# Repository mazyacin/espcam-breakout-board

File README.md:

# espcam-breakout-board
high-end ESP32-Cam breakout-board for IOT and monetering systems , so there has been a problem with the espcam and its the programming because it does not have a USB to UART converter so i am making a breakout board for it that solves that problem and adds more features like :tp5100 for charging ,MT3608 for 5v,3.3v,output, bme280 for IOT  also an IMU mpu6000 ,BMS( DW01A protection IC with 2 mosfets), 
it supports 4.2v batteries and cells any higher voltage will cut the power because the BMS is for 1s configuration, the charging is at 2A, bme temperature accuracy is ±0.5°C and humidity ±3%  Barometric Pressure ±1.0 hPa its set to i2c and its address is 0x76 or 0x77, mpu6000 is switched to i2c (cs pin is high) and address 0x69 accuracy Gyro: ±250 to ±2000 °/s accelerometer ±2g to ±16g internal tempurature sensor ±1°C

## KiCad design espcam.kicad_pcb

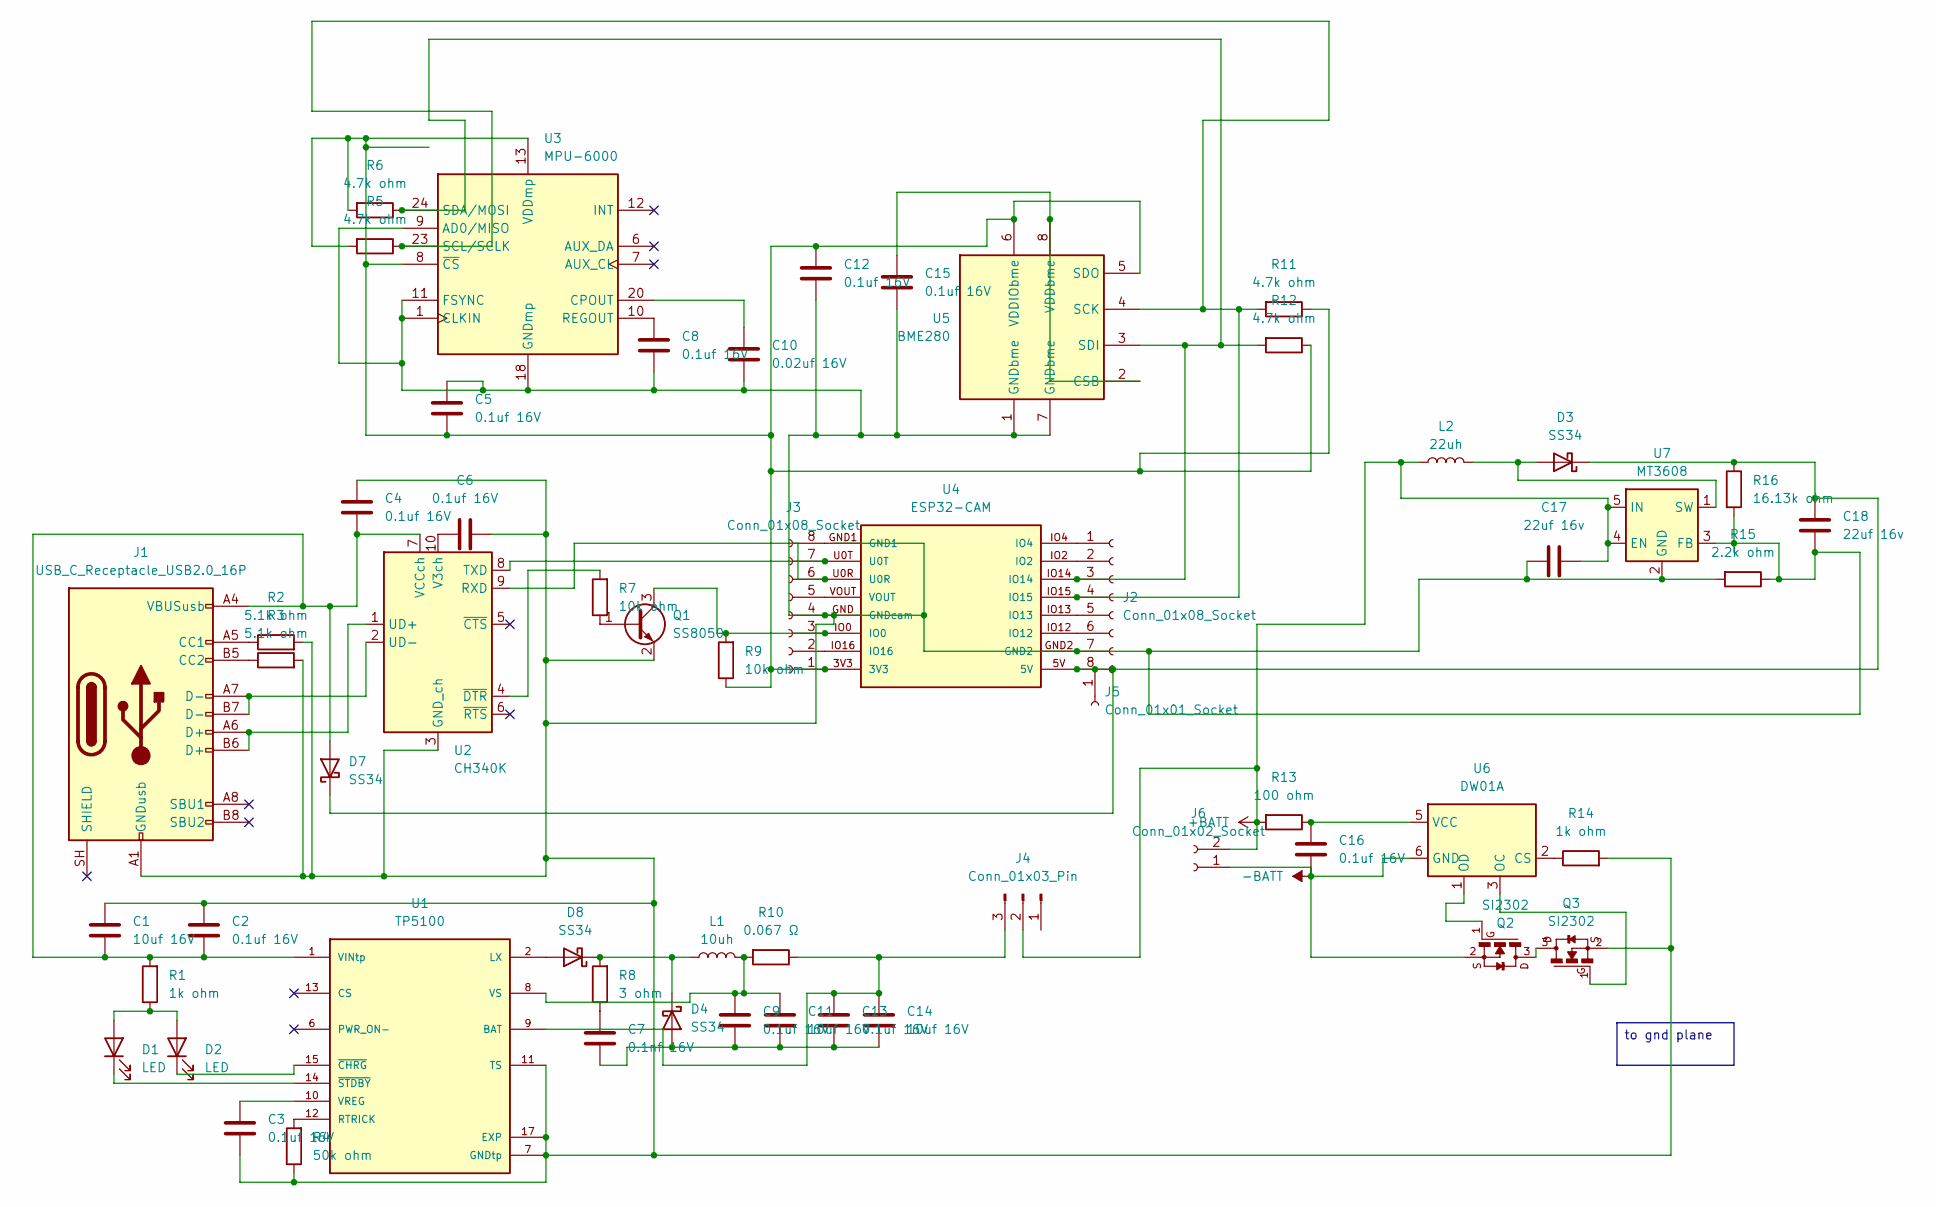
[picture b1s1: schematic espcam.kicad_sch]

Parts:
C1, C11, C14: 10uf 16V; C_1206_3216Metric
C2, C3, C4, C5, C6, C8, C9, C12, C13, C15, C16: 0.1uf 16V; C_0603_1608Metric
C7: 0.1nf 16V; C_0603_1608Metric
C10: 0.02uf 16V; C_0603_1608Metric
C17, C18: 22uf 16v; C_1206_3216Metric
D1, D2: LED; LED_0603_1608Metric
D3, D4, D7, D8: SS34; D_SMA
J1: USB_C_Receptacle_USB2.0_16P; USB_C_Receptacle_G-Switch_GT-USB-7010ASV
J2, J3: Conn_01x08_Socket; PinSocket_1x08_P2.54mm_Vertical
J4: Conn_01x03_Pin; PinHeader_1x03_P2.54mm_Vertical
J5: Conn_01x01_Socket; PinSocket_1x01_P2.54mm_Vertical
J6: Conn_01x02_Socket; TerminalBlock_Phoenix_MKDS-1,5-2-5.08_1x02_P5.08mm_Horizont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
L1: 10uh; L_Taiyo-Yuden_NR-60xx
L2: 22uh; L_Taiyo-Yuden_NR-60xx
Q1: SS8050; SOT-23
Q2, Q3: SI2302; SOT23
R1, R14: 1k ohm; R_0603_1608Metric
R2, R3: 5.1k ohm; R_0603_1608Metric
R4: 50k ohm; R_0603_1608Metric
R5, R6, R11, R12: 4.7k ohm; R_0603_1608Metric
R7, R9: 10k ohm; R_0603_1608Metric
R8: 3 ohm; R_0603_1608Metric
R10: 0.067 Ω; R_1206_3216Metric
R13: 100 ohm; R_0603_1608Metric
R15: 2.2k ohm; R_0603_1608Metric
R16: 16.13k ohm; R_0603_1608Metric
U1: TP5100; PARTREV 2.3; LCSC C379389
U2: CH340K; SSOP-10-1EP_3.9x4.9mm_P1mm_EP2.1x3.3mm; LCSC C968586
U3: MPU-6000; InvenSense_QFN-24_4x4mm_P0.5mm
U4: ESP32-CAM
U5: BME280; Bosch_LGA-8_2.5x2.5mm_P0.65mm_ClockwisePinNumbering; LCSC C92489
U6: DW01A; SOT-23-6; LCSC C11702
U7: MT3608; SOT-23-6; LCSC C83247

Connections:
+BATT: C17.2, J4.2, J6.2, L2.1, R13.2, U7.4 (EN), U7.5 (IN)
-BATT: C16.2, J6.1, Q2.2, U6.6 (GND)
unnamed: C7.1, R8.1
unnamed: D1.2 (A), D2.2 (A), R1.1
unnamed: D1.1 (K), U1.14 (~STDBY)
unnamed: D2.1 (K), U1.15 (~CHRG)
unnamed: D3.2 (A), L2.2, U7.1 (SW)
unnamed 7: C18.1, D3.1 (K), D7.1 (K), J2.8, J5.1, R16.1, U4.5V; also elsewhere on the board
unnamed: C7.2, C9.2, C11.2, C13.2, C14.2, D4.2 (A)
unnamed: D4.1 (K), D8.1 (K), L1.1, R8.2
unnamed: C1.2, C2.2, C4.2, D7.2 (A), J1.A4 (VBUSusb), J1.A9 (VBUS), J1.B4 (VBUS), J1.B9 (VBUS), R1.2, U1.1 (VINtp), U1.4 (VIN), U1.5 (VIN), U1.16 (VIN), U2.7 (VCCch)
unnamed: D8.2 (A), U1.2 (LX), U1.3 (LX)
unnamed: J1.A5 (CC1), R2.1
unnamed: J1.B5 (CC2), R3.1
unnamed: C1.1, C2.1, C3.2, C4.1, C5.1, C6.2, C8.2, C10.2, C12.2, C15.2, C17.1, C18.2, J1.A1 (GNDusb), J1.A12 (GND), J1.B1 (GND), J1.B12 (GND), J2.7, J3.4, Q1.2 (E), Q3.2, R2.2, R3.2, R4.1, R14.2, R15.1, R15.2, R16.2, U1.7 (GNDtp), U1.11 (TS), U1.17 (EXP), U2.3 (GND_ch), U2.11 (GND), U3.1 (CLKIN), U3.9 (AD0/MISO), U3.11 (FSYNC), U3.18 (GNDmp), U4.GND (GNDcam), U4.GND2, U5.1 (GNDbme), U5.7 (GNDbme), U7.2 (GND), U7.3 (FB)
unnamed: J2.1, U4.IO4
unnamed: J2.2, U4.IO2
unnamed: J2.3, R6.1, R12.2, U3.24 (SDA/MOSI), U4.IO14, U5.3 (SDI)
unnamed: J2.4, R5.1, R11.2, U3.23 (SCL/SCLK), U4.IO15, U5.4 (SCK)
unnamed: J2.5, U4.IO13
unnamed: J2.6, U4.IO12
unnamed: C5.2, C12.1, J3.1, R5.2, R6.2, R9.1, R11.1, R12.1, U3.8 (~CS), U3.13 (VDDmp), U4.3V3, U5.5 (SDO), U5.6 (VDDIObme)
unnamed: J3.2, U4.IO16
unnamed: J3.3, Q1.3 (C), R9.2, U4.IO0
unnamed: J3.5, U4.VOUT
unnamed: J3.6, U2.9 (RXD), U4.U0R
unnamed: J3.7, U2.8 (TXD), U4.U0T
unnamed: J3.8, U4.GND1
unnamed: C13.1, C14.1, J4.3, R10.1, U1.9 (BAT)
unnamed: Q1.1 (B), R7.1
unnamed: Q2.3, Q3.3
unnamed: R4.2, U1.12 (RTRICK)
unnamed: C3.1, U1.10 (VREG)
unnamed: C9.1, C11.1, L1.2, R10.2, U1.8 (VS)
unnamed: J1.A6 (D+), J1.B6 (D+), U2.1 (UD+)
unnamed: J1.A7 (D-), J1.B7 (D-), U2.2 (UD-)
unnamed: C6.1, U2.10 (V3ch)
unnamed: R7.2, U2.4 (~DTR)
unnamed: C10.1, U3.20 (CPOUT)
unnamed: C8.1, U3.10 (REGOUT)
unnamed: C15.1, U5.2 (CSB), U5.8 (VDDbme)
unnamed: R14.1, U6.2 (CS)
unnamed: Q3.1, U6.3 (OC)
unnamed: Q2.1, U6.1 (OD)
unnamed: C16.1, R13.1, U6.5 (VCC)

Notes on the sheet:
to gnd plane

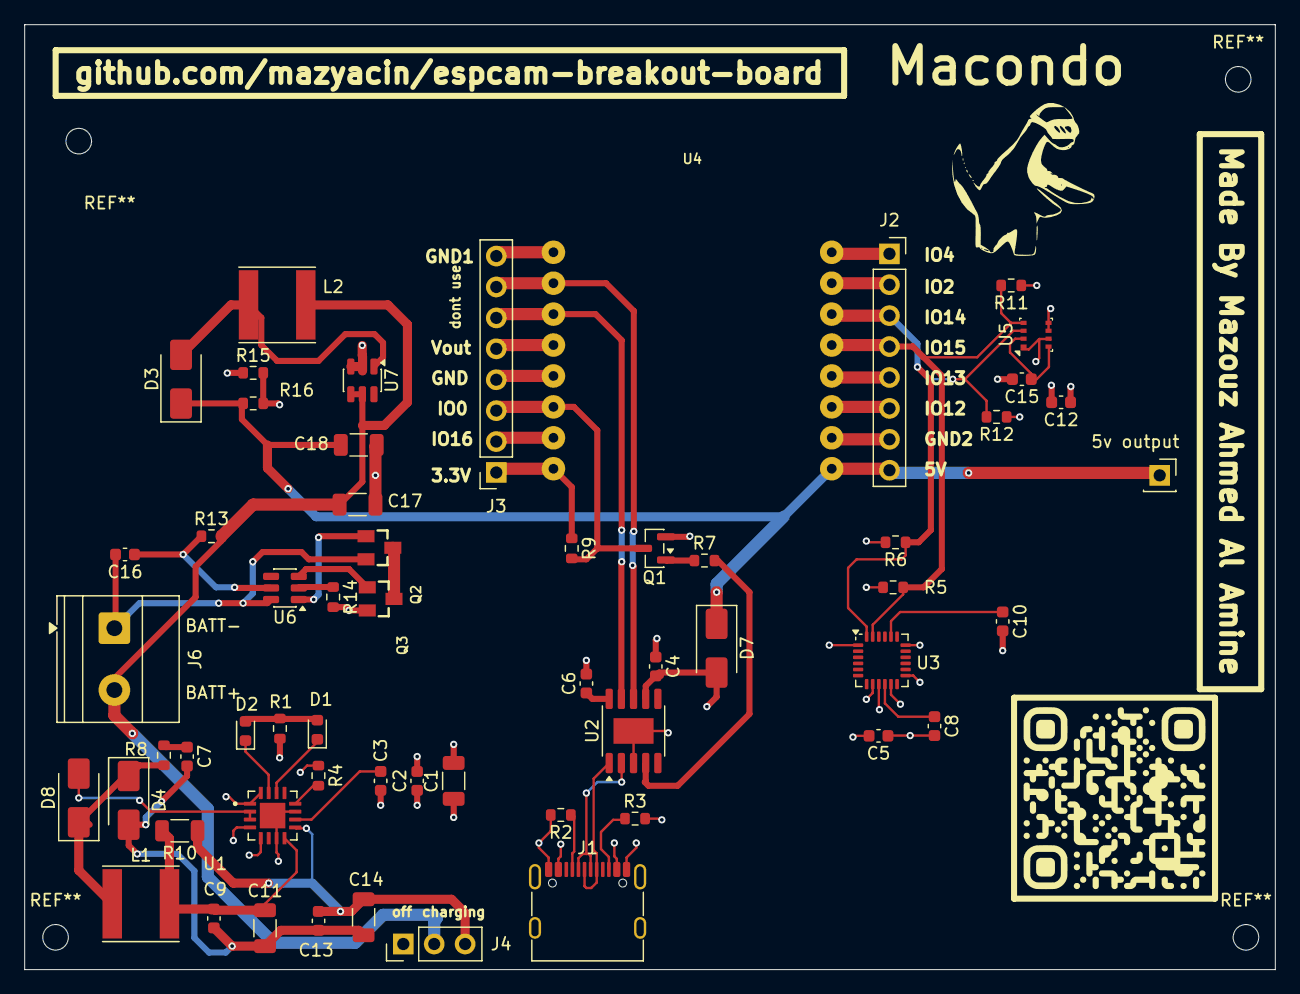
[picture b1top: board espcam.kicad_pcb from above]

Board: 4 copper layers, 102.7 x 77.6 mm, 58 parts (0 on the bottom side), 45 nets.

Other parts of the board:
5v output: Conn_01x01_Socket; PinSocket_1x01_P2.54mm_Vertical

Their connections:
unnamed 7: 5v output.1 (Pin_1_1); also elsewhere on the board
